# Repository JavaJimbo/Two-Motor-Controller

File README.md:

# Two-Motor-Controller
Eagle PCB files for PIC 32MX220 controller with two IFX9201SG H bridges

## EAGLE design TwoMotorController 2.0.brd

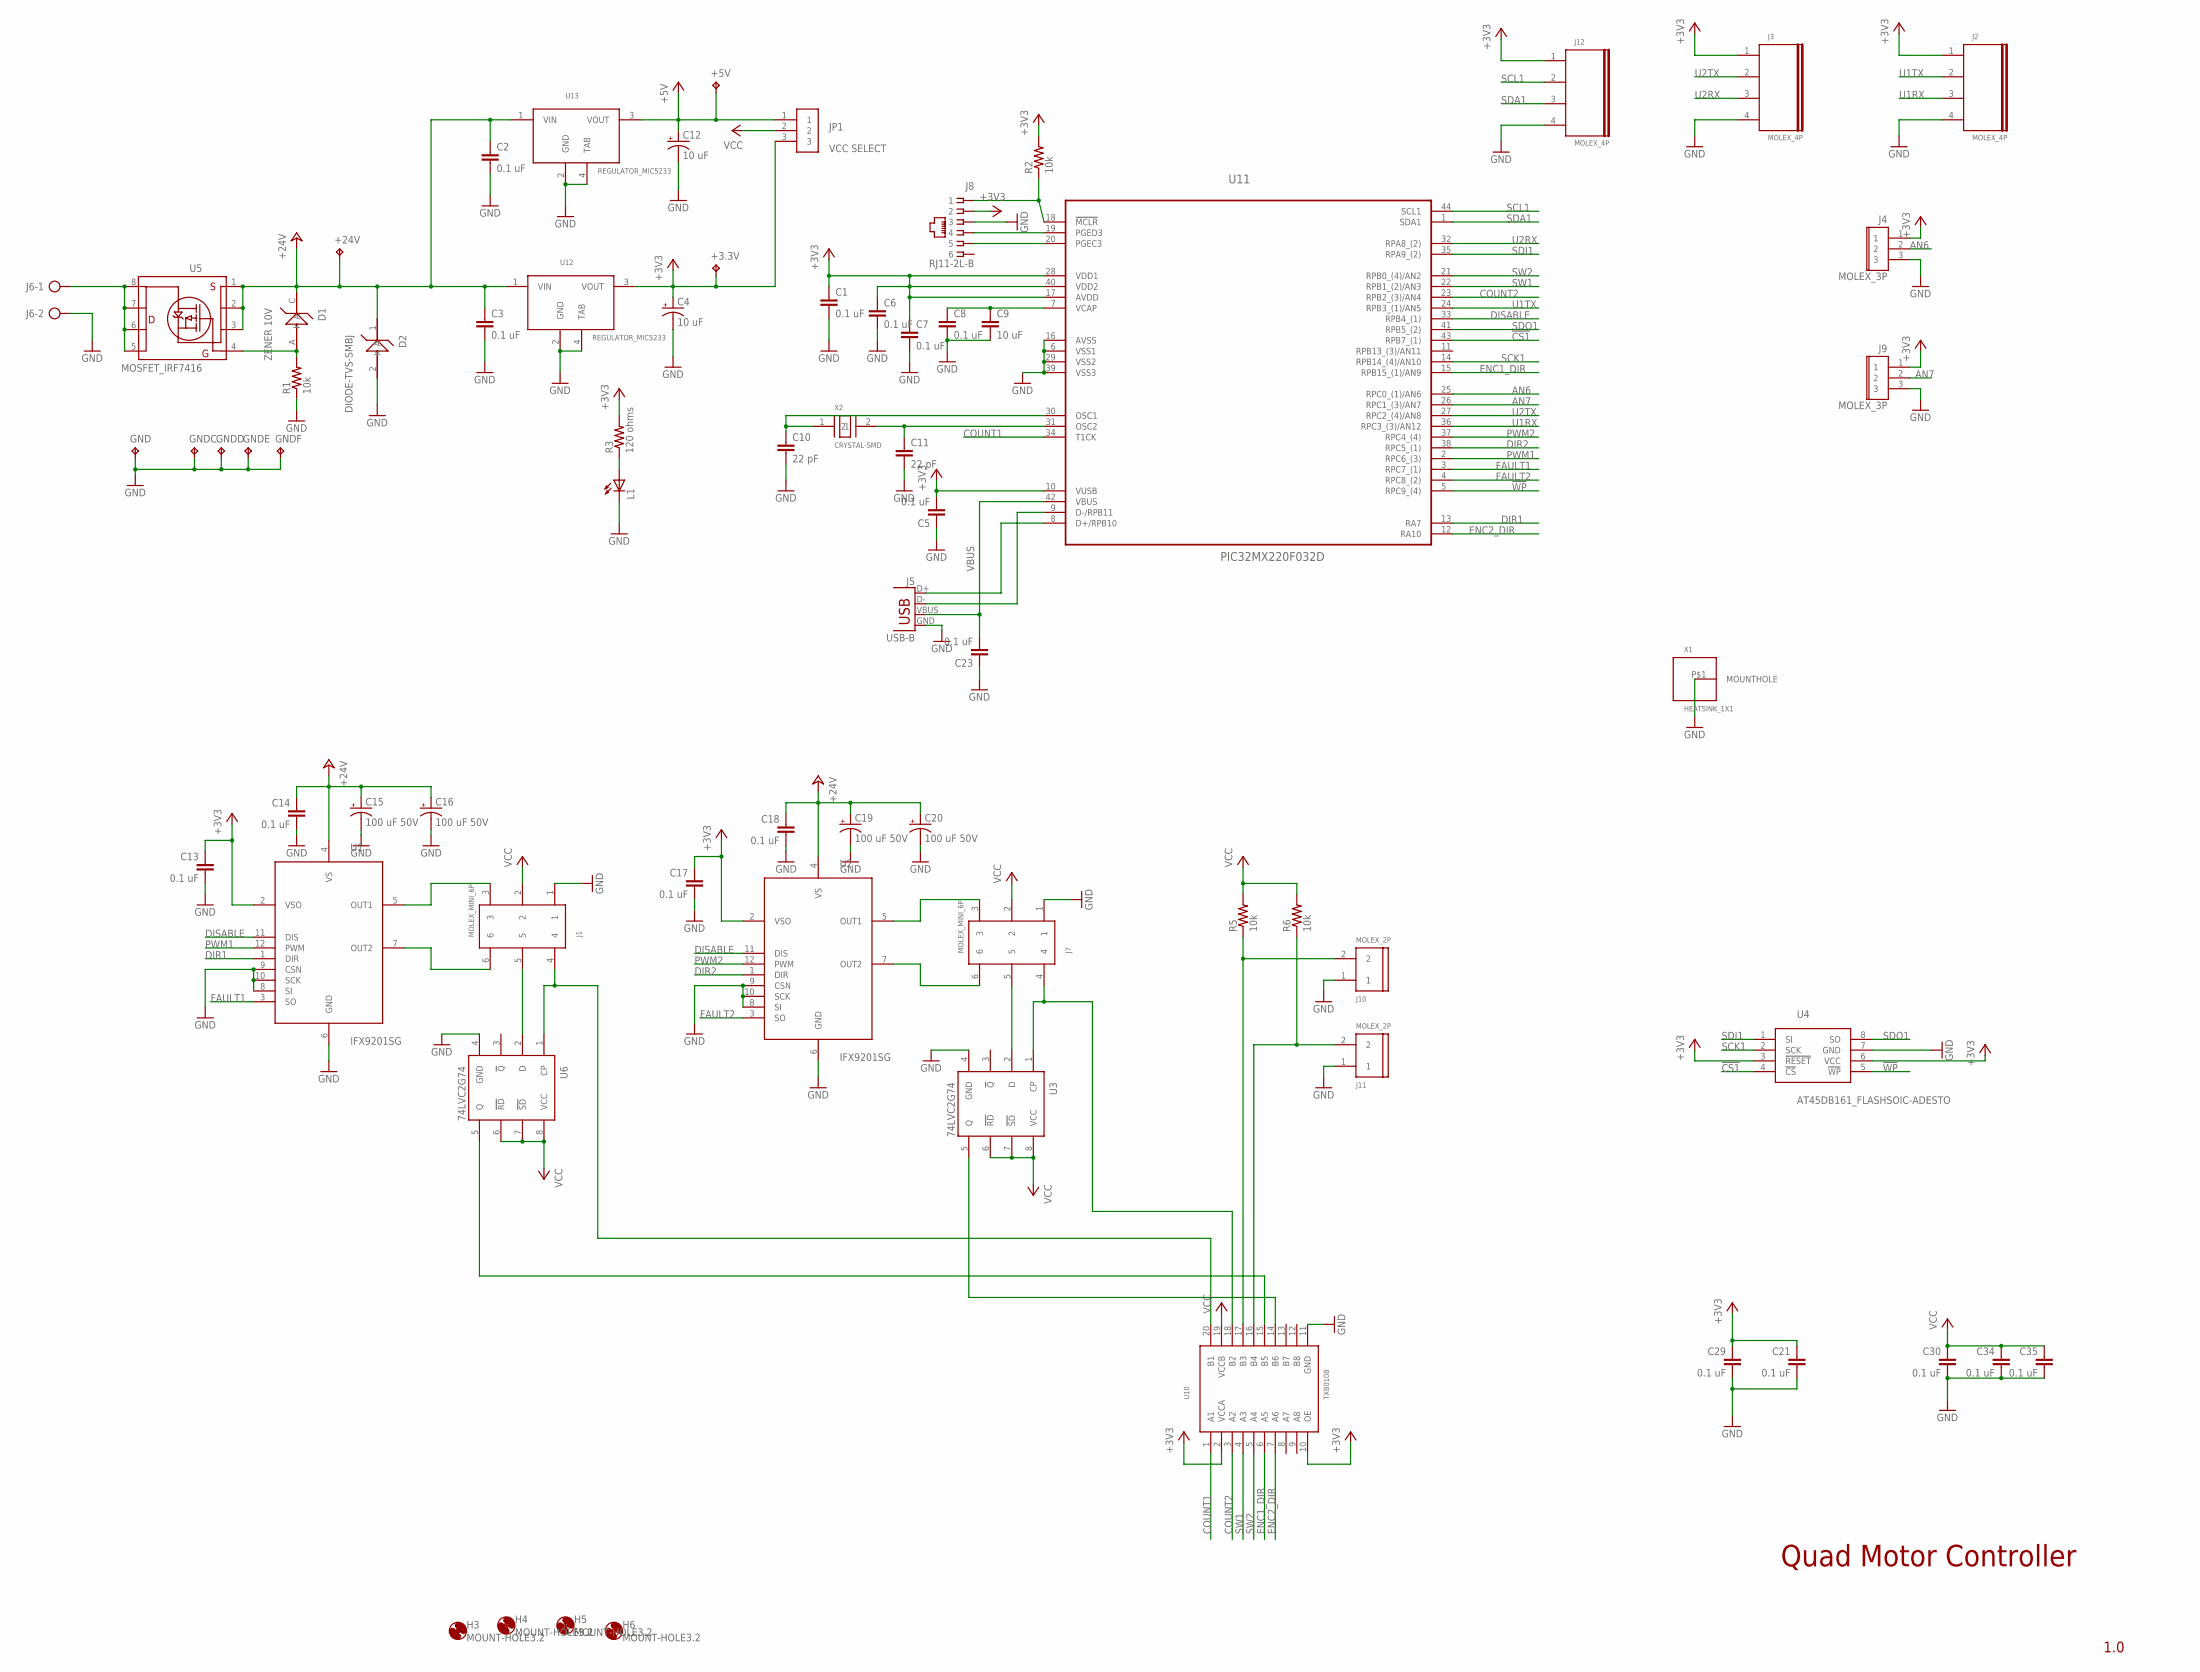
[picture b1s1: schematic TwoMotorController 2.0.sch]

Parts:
+3.3V, +5V, +24V: TP; TESTPAD
C1, C2, C3, C6, C7, C8, C13, C14, C17, C18, C21, C29, C30, C34, C35: 0.1 uF; C0805
C4, C12: 10 uF; POLCAP_2MM
C5, C23: 0.1 uF; C2.5-3
C9: 10 uF; C0805
C10, C11: 22 pF; C0805
C15, C16, C19, C20: 100 uF 50V; E3,5-10
D1: ZENER 10V; DO-214AC
D2: DIODE-TVS-SMBJ
GND: TP; TESTPAD
GNDC: TP; TESTPAD
GNDD: TP; TESTPAD
GNDE: TP; TESTPAD
GNDF: TP; TESTPAD
H3, H4, H5, H6: MOUNT-HOLE3.2; 3,2
J1, J7: MOLEX_MINI_6P
J2, J3, J12: MOLEX_4P
J4, J9: MOLEX_3P
J5: USB-B; USB-B-PTH
J6: TRMBLOCK_5MM_2P
J8: RJ11-2L-B; RJ11-NO_SHIELD
J10, J11: MOLEX_2P
JP1: VCC SELECT; JUMPER_3P
L1: LED5MM
R1, R2, R5, R6: 10k; R0805
R3: 120 ohms; R0805
U1, U2: IFX9201SG
U3, U6: 74LVC2G74; TSSOP8
U4: AT45DB161_FLASHSOIC-ADESTO; SOIC-ADESTO
U5: MOSFET_IRF7416; SO-8-3.9MM
U10: TXB0108; TSSOP20
U11: PIC32MX220F032D; QFP80P1200X1200X120-44N
U12, U13: REGULATOR_MIC5233
X1: HEATSINK_1X1
X2: CRYSTAL-SMD

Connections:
!CS1: U4.4 (!CS), U11.43 (RPB7_(1))
!WP: U4.5 (!WP), U11.5 (RPC9_(4))
+3V3: +3.3V.P$1, C1.1, C4.+, C5.2, C6.1, C7.1, C13.1, C17.1, C21.1, C29.1, J2.1, J3.1, J4.1, J8.2, J9.1, J12.1, JP1.3, R2.2, R3.2, U1.2 (VSO), U2.2 (VSO), U4.3 (!RESET), U4.6 (VCC), U10.2 (VCCA), U10.10 (OE), U11.10 (VUSB), U11.17 (AVDD), U11.28 (VDD1), U11.40 (VDD2), U12.3 (VOUT)
+5V: +5V.P$1, C12.+, JP1.1, U13.3 (VOUT)
+24V: +24V.P$1, C2.1, C3.1, C14.1, C15.+, C16.+, C18.1, C19.+, C20.+, D1.C (K), D2.1 (K), U1.4 (VS), U2.4 (VS), U5.1, U5.2, U5.3, U12.1 (VIN), U13.1 (VIN)
AN6: J4.2, U11.25 (RPC0_(1)/AN6)
AN7: J9.2, U11.26 (RPC1_(3)/AN7)
COUNT1: U10.1 (A1), U11.34 (T1CK)
COUNT2: U10.3 (A2), U11.23 (RPB2_(3)/AN4)
DIR1: U1.1 (DIR), U11.13 (RA7)
DIR2: U2.1 (DIR), U11.38 (RPC5_(1))
DISABLE: U1.11 (DIS), U2.11 (DIS), U11.33 (RPB4_(1))
ENC1_DIR: U10.6 (A5), U11.15 (RPB15_(1)/AN9)
ENC2_DIR: U10.7 (A6), U11.12 (RA10)
FAULT1: U1.3 (SO), U11.3 (RPC7_(1))
FAULT2: U2.3 (SO), U11.4 (RPC8_(2))
GND: C1.2, C2.2, C3.2, C4.-, C5.1, C6.2, C7.2, C8.2, C9.2, C10.2, C11.2, C12.-, C13.2, C14.2, C15.-, C16.-, C17.2, C18.2, C19.-, C20.-, C21.2, C23.1, C29.2, C30.2, C34.2, C35.2, D2.2 (A), GND.P$1, GNDC.P$1, GNDD.P$1, GNDE.P$1, GNDF.P$1, J1.1, J2.4, J3.4, J4.3, J5.GND, J6.2, J7.1, J8.3, J9.3, J10.1, J11.1, J12.4, L1.K (C), R1.1, U1.6 (GND), U1.8 (SI), U1.9 (CSN), U1.10 (SCK), U2.6 (GND), U2.8 (SI), U2.9 (CSN), U2.10 (SCK), U3.4 (GND), U4.7 (GND), U6.4 (GND), U10.11 (GND), U11.6 (VSS1), U11.16 (AVSS), U11.29 (VSS2), U11.39 (VSS3), U12.2 (GND), U12.4 (TAB), U13.2 (GND), U13.4 (TAB), X1.P$1
unnamed: J7.3, U2.5 (OUT1)
unnamed: C11.1, U11.31 (OSC2), X2.2
unnamed: C10.1, U11.30 (OSC1), X2.1
unnamed: J1.3, U1.5 (OUT1)
unnamed: J6.1, U5.5, U5.6, U5.7, U5.8
unnamed: D1.A, R1.2, U5.4
unnamed: J1.6, U1.7 (OUT2)
unnamed: J1.5, U6.2 (D)
unnamed: U6.5 (Q), U10.15 (B5)
unnamed: J8.1, R2.1, U11.18 (!MCLR)
unnamed: J8.4, U11.19 (PGED3)
unnamed: J8.5, U11.20 (PGEC3)
unnamed: C8.1, C9.1, U11.7 (VCAP)
unnamed: J7.6, U2.7 (OUT2)
unnamed: J7.5, U3.2 (D)
unnamed: U3.5 (Q), U10.14 (B6)
unnamed: J10.2, R5.1, U10.17 (B3)
unnamed: J11.2, R6.1, U10.16 (B4)
unnamed: J5.D+, U11.8 (D+/RPB10)
unnamed: J5.D-, U11.9 (D-/RPB11)
unnamed: L1.A, R3.1
unnamed: J1.4, U6.1 (CP), U10.20 (B1)
unnamed: J7.4, U3.1 (CP), U10.18 (B2)
PWM1: U1.12 (PWM), U11.2 (RPC6_(3))
PWM2: U2.12 (PWM), U11.37 (RPC4_(4))
SCK1: U4.2 (SCK), U11.14 (RPB14_(4)/AN10)
SCL1: J12.2, U11.44 (SCL1)
SDA1: J12.3, U11.1 (SDA1)
SDI1: U4.1 (SI), U11.35 (RPA9_(2))
SDO1: U4.8 (SO), U11.41 (RPB5_(2))
SW1: U10.4 (A3), U11.22 (RPB1_(2)/AN3)
SW2: U10.5 (A4), U11.21 (RPB0_(4)/AN2)
U1RX: J2.3, U11.36 (RPC3_(3)/AN12)
U1TX: J2.2, U11.24 (RPB3_(1)/AN5)
U2RX: J3.3, U11.32 (RPA8_(2))
U2TX: J3.2, U11.27 (RPC2_(4)/AN8)
VBUS: C23.2, J5.VBUS, U11.42 (VBUS)
VCC: C30.1, C34.1, C35.1, J1.2, J7.2, JP1.2, R5.2, R6.2, U3.6 (!RD), U3.7 (!SD), U3.8 (VCC), U6.6 (!RD), U6.7 (!SD), U6.8 (VCC), U10.19 (VCCB)

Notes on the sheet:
Quad Motor Controller
1.0

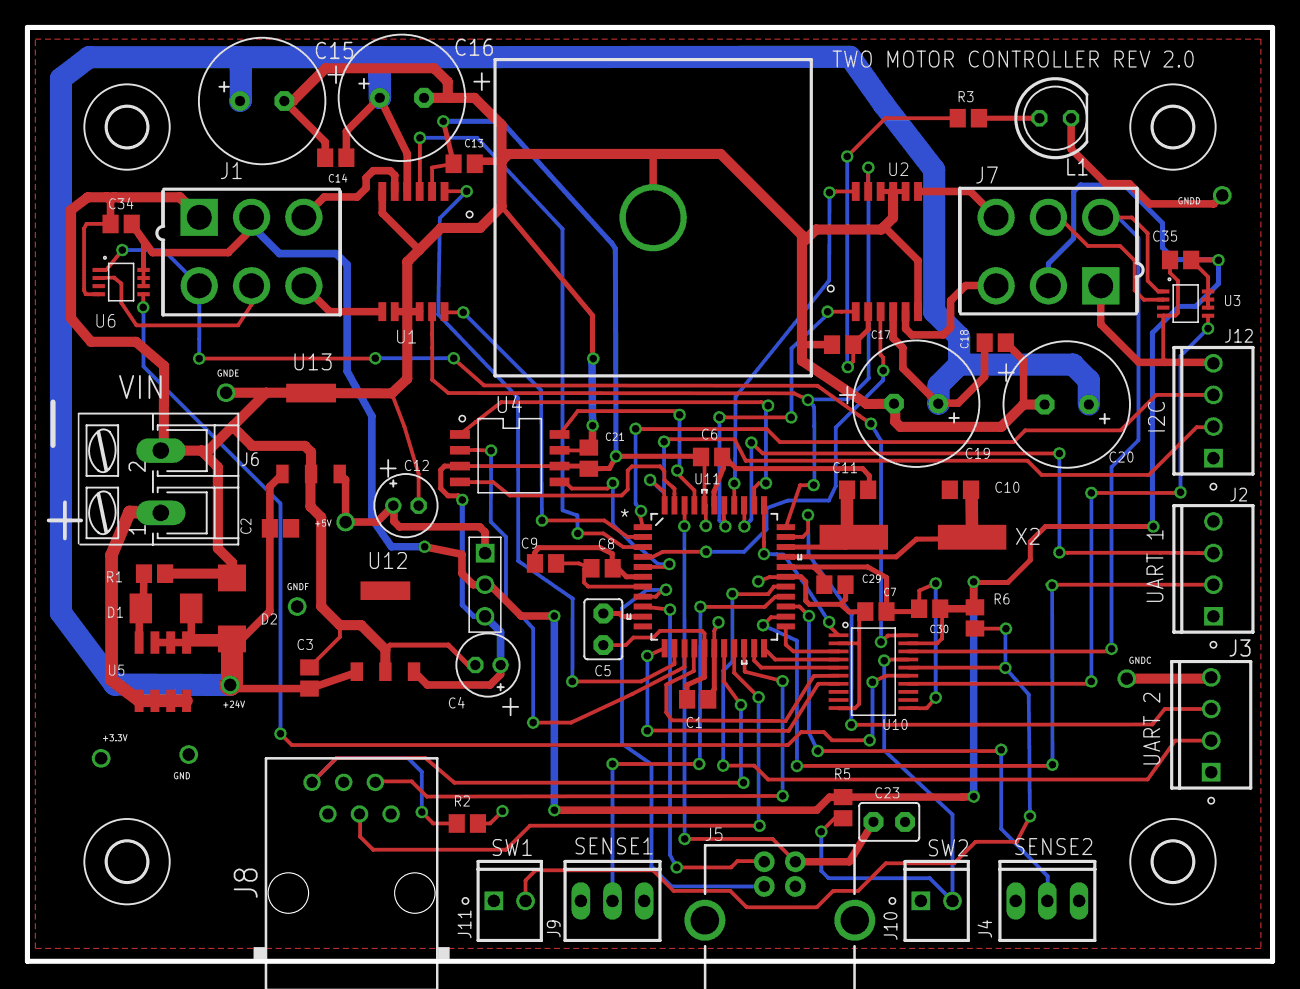
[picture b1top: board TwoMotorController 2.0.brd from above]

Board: 2 copper layers, 100.0 x 75.0 mm, 71 parts (0 on the bottom side), 55 nets.

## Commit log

2017-07-17 Add files via upload
    This is a 4" x 3" two layer PCB with two IFX9201SG H bridges
    and 0.1" Molex connectors for IO and UARTs.
    V2.0 includes USB.

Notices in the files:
parts and their libraries:
SparkFun-Connectors: Licensing: Creative Commons ShareAlike 4.0 International - https://creativecommons.org/licenses/by-sa/4.0
